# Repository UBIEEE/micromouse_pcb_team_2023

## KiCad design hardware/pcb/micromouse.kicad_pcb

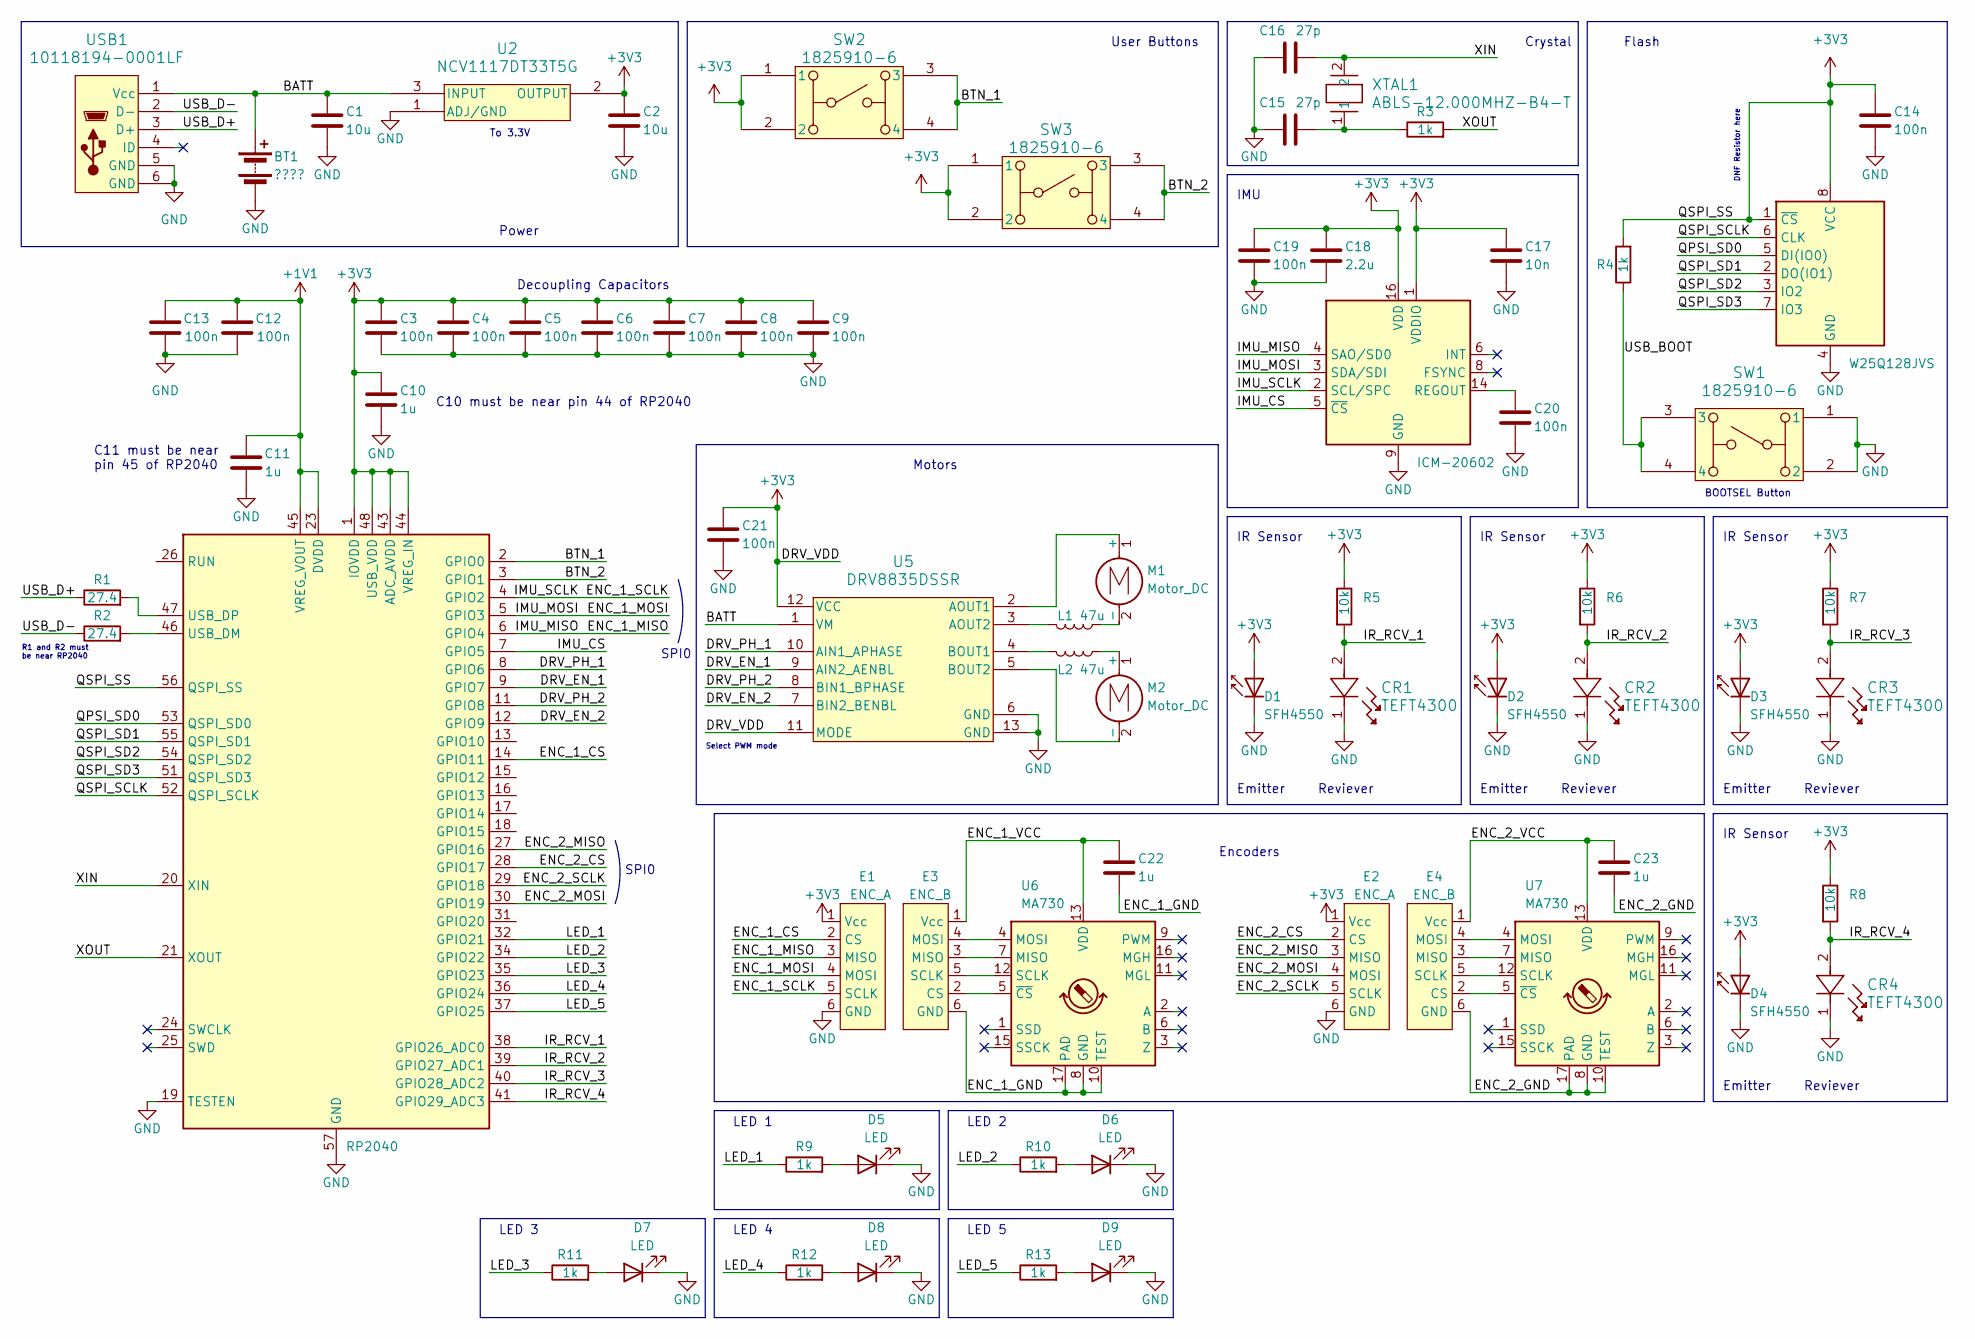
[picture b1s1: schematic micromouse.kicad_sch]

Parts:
BT1: ????; CONN_B2B-ZRLFSN_JST
C1, C2: 10u; CAP_GRM21_MUR
C3, C4, C5, C6, C7, C8, C9, C12, C13, C14, C19, C20, C21: 100n; CAP_GRM155_MUR
C10, C11, C22, C23: 1u; CAP_GRM155_MUR
C15, C16: 27p; CAP_GCM155_MUR
C17: 10n; CAP_GRM1885_1P6XP8_MUR
C18: 2.2u; CAP_GRM155_MUR
CR1, CR2, CR3, CR4: TEFT4300
D1, D2, D3, D4: SFH4550
D5, D6, D7, D8, D9: LED; LED_LTST-C191_LTO
E1: ENC_A; ENC_1_A
E2: ENC_A; ENC_2_A
E3: ENC_B; ENC_1_B
E4: ENC_B; ENC_2_B
L1, L2: 47u; IND_BOURNS_SRR4028
M1, M2: Motor_DC; CONN_B2B-ZRLFSN_JST
R1, R2: 27.4; RES_RC0402_YAG
R3, R4, R9, R10, R11, R12, R13: 1k; RES_RC0402_YAG
R5, R6, R7, R8: 10k; RES_RC0402_YAG
SW1, SW2, SW3: 1825910-6; SW4_1825910-B_TEC
U1: RP2040; QFN-56-1EP_7x7mm_P0.4mm_EP3.2x3.2mm
U2: NCV1117DT33T5G; DPAK-3_ONS
U3: W25Q128JVS; SOIC-8_5.23x5.23mm_P1.27mm
U4: ICM-20602; LGA-16_3x3mm_P0.5mm_LayoutBorder3x5y
U5: DRV8835DSSR; DSS0012A
U6, U7: MA730; QFN-16-1EP_3x3mm_P0.5mm_EP1.75x1.75mm
USB1: 10118194-0001LF; CONN_10118194-0001LF_AMP
XTAL1: ABLS-12.000MHZ-B4-T; XTAL_ABLS_ABR

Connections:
+1V1: C11.2, C12.2, C13.2, U1.23 (DVDD), U1.45 (VREG_VOUT), U1.50 (DVDD)
+3V3: C2.1, C3.1, C4.1, C5.1, C6.1, C7.1, C8.1, C9.1, C10.1, C14.1, C17.1, C18.1, C19.1, C21.1, D1.2 (A), D2.2 (A), D3.2 (A), D4.2 (A), E1.1 (Vcc), E2.1 (Vcc), R4.2, R5.1, R6.1, R7.1, R8.1, SW2.1, SW2.2, SW3.1, SW3.2, U1.1 (IOVDD), U1.10 (IOVDD), U1.22 (IOVDD), U1.33 (IOVDD), U1.42 (IOVDD), U1.43 (ADC_AVDD), U1.44 (VREG_IN), U1.48 (USB_VDD), U1.49 (IOVDD), U1.56 (QSPI_SS), U2.2 (OUTPUT), U3.1 (~CS), U3.8 (VCC), U4.1 (VDDIO), U4.16 (VDD), U5.11 (MODE), U5.12 (VCC)
/BATT: BT1.1 (+), C1.1, U2.3 (INPUT), U5.1 (VM), USB1.1 (Vcc)
/BTN_1: SW2.3, SW2.4, U1.2 (GPIO0)
/BTN_2: SW3.3, SW3.4, U1.3 (GPIO1)
/DRV_EN_1: U1.9 (GPIO7), U5.9 (AIN2_AENBL)
/DRV_EN_2: U1.12 (GPIO9), U5.7 (BIN2_BENBL)
/DRV_PH_1: U1.8 (GPIO6), U5.10 (AIN1_APHASE)
/DRV_PH_2: U1.11 (GPIO8), U5.8 (BIN1_BPHASE)
/ENC_1_CS: E1.2 (CS), U1.14 (GPIO11)
/ENC_1_GND: C22.2, E3.6 (GND), U6.8 (GND), U6.10 (TEST), U6.17 (PAD)
/ENC_1_MISO: E1.3 (MISO), U1.6 (GPIO4), U4.4 (SAO/SD0)
/ENC_1_MOSI: E1.4 (MOSI), U1.5 (GPIO3), U4.3 (SDA/SDI)
/ENC_1_SCLK: E1.5 (SCLK), U1.4 (GPIO2), U4.2 (SCL/SPC)
/ENC_1_VCC: C22.1, E3.1 (Vcc), U6.13 (VDD)
/ENC_2_CS: E2.2 (CS), U1.28 (GPIO17)
/ENC_2_GND: C23.2, E4.6 (GND), U7.8 (GND), U7.10 (TEST), U7.17 (PAD)
/ENC_2_MISO: E2.3 (MISO), U1.27 (GPIO16)
/ENC_2_MOSI: E2.4 (MOSI), U1.30 (GPIO19)
/ENC_2_SCLK: E2.5 (SCLK), U1.29 (GPIO18)
/ENC_2_VCC: C23.1, E4.1 (Vcc), U7.13 (VDD)
/IMU_CS: U1.7 (GPIO5), U4.5 (~CS)
/IR_RCV_1: CR1.2, R5.2, U1.38 (GPIO26_ADC0)
/IR_RCV_2: CR2.2, R6.2, U1.39 (GPIO27_ADC1)
/IR_RCV_3: CR3.2, R7.2, U1.40 (GPIO28_ADC2)
/IR_RCV_4: CR4.2, R8.2, U1.41 (GPIO29_ADC3)
/LED_1: R9.1, U1.32 (GPIO21)
/LED_2: R10.1, U1.34 (GPIO22)
/LED_3: R11.1, U1.35 (GPIO23)
/LED_4: R12.1, U1.36 (GPIO24)
/LED_5: R13.1, U1.37 (GPIO25)
/QPSI_SD0: U1.53 (QSPI_SD0), U3.5 (DI(IO0))
/QSPI_SCLK: U1.52 (QSPI_SCLK), U3.6 (CLK)
/QSPI_SD1: U1.55 (QSPI_SD1), U3.2 (DO(IO1))
/QSPI_SD2: U1.54 (QSPI_SD2), U3.3 (IO2)
/QSPI_SD3: U1.51 (QSPI_SD3), U3.7 (IO3)
/USB_BOOT: R4.1, SW1.3, SW1.4
/USB_D+: R1.1, USB1.3 (D+)
/USB_D-: R2.1, USB1.2 (D-)
/XIN: C16.2, U1.20 (XIN), XTAL1.2
/XOUT: R3.2, U1.21 (XOUT)
GND: BT1.2 (-), C1.2, C2.2, C3.2, C4.2, C5.2, C6.2, C7.2, C8.2, C9.2, C10.2, C11.1, C12.1, C13.1, C14.2, C15.1, C16.1, C17.2, C18.2, C19.2, C20.2, C21.2, CR1.1, CR2.1, CR3.1, CR4.1, D1.1 (K), D2.1 (K), D3.1 (K), D4.1 (K), D5.1 (K), D6.1 (K), D7.1 (K), D8.1 (K), D9.1 (K), E1.6 (GND), E2.6 (GND), SW1.1, SW1.2, U1.19 (TESTEN), U1.57 (GND), U2.1 (ADJ/GND), U3.4 (GND), U4.9 (GND), U4.10 (GND), U4.11 (GND), U4.12 (GND), U4.13 (GND), U4.15 (GND), U5.6 (GND), U5.13 (GND), USB1.5 (GND), USB1.6 (GND)
unnamed: C15.2, R3.1, XTAL1.1
unnamed: D5.2 (A), R9.2
unnamed: D6.2 (A), R10.2
unnamed: D7.2 (A), R11.2
unnamed: D8.2 (A), R12.2
unnamed: D9.2 (A), R13.2
unnamed: E3.2 (CS), U6.5 (~CS)
unnamed: E3.3 (MISO), U6.7 (MISO)
unnamed: E3.4 (MOSI), U6.4 (MOSI)
unnamed: E3.5 (SCLK), U6.12 (SCLK)
unnamed: E4.2 (CS), U7.5 (~CS)
unnamed: E4.3 (MISO), U7.7 (MISO)
unnamed: E4.4 (MOSI), U7.4 (MOSI)
unnamed: E4.5 (SCLK), U7.12 (SCLK)
unnamed: M1.1 (+), U5.2 (AOUT1)
unnamed: L1.1, M1.2 (-)
unnamed: L2.1, M2.1 (+)
unnamed: M2.2 (-), U5.5 (BOUT2)
unnamed: R2.2, U1.46 (USB_DM)
unnamed: R1.2, U1.47 (USB_DP)
unnamed: C20.1, U4.14 (REGOUT)
unnamed: L1.2, U5.3 (AOUT2)
unnamed: L2.2, U5.4 (BOUT1)

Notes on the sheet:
Decoupling Capacitors
User Buttons
Emitter
Reviever
LED 4
LED 3
Flash
Crystal
DNF Resistor here
Select PWM mode
Power
SPI0
R1 and R2 must be near RP2040
IR Sensor
BOOTSEL Button
Encoders
C11 must be near pin 45 of RP2040
To 3.3V
LED 5
LED 1
C10 must be near pin 44 of RP2040
LED 2
IMU
Motors

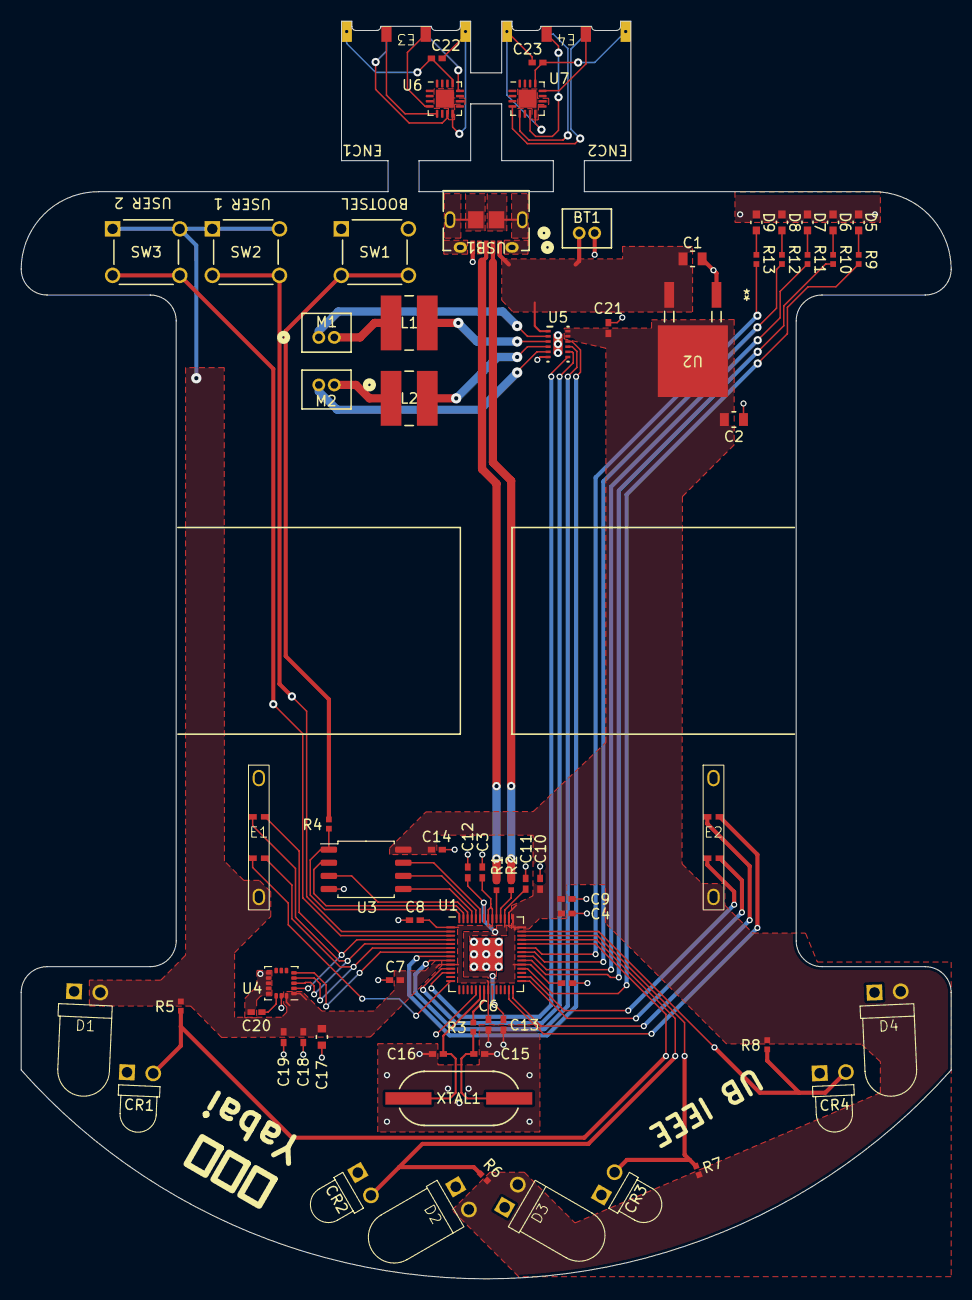
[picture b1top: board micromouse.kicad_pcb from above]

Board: 2 copper layers, 90.0 x 121.7 mm, 70 parts (0 on the bottom side), 65 nets.

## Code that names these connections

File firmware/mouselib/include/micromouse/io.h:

#ifndef __MICROMOUSE_IO_H__
#define __MICROMOUSE_IO_H__

#define PIN_BTN_1 0
#define PIN_BTN_2 1

// SPI 0
#define PIN_IMU_R_ENC_SCLK 2
#define PIN_IMU_R_ENC_MOSI 3
#define PIN_IMU_R_ENC_MISO 4
#define PIN_IMU_CS         5

#define PIN_L_MOT_PH 6
#define PIN_L_MOT_EN 7

#define PIN_R_MOT_PH 8
#define PIN_R_MOT_EN 9

// 10 - Unused

#define PIN_R_ENC_CS 11

// 12 - Unused
// 13 - Unused
// 14 - Unused
// 15 - Unused

// SPI 0
#define PIN_L_ENC_SCLK 18
#define PIN_L_ENC_MOSI 19
#define PIN_L_ENC_MISO 16
#define PIN_L_ENC_CS   17

// 20 - Unused

#define PIN_LED_1 21
#define PIN_LED_2 22
#define PIN_LED_3 23
#define PIN_LED_4 24
#define PIN_LED_5 25

#define PIN_ADC_0 26
#define PIN_ADC_1 27
#define PIN_ADC_2 28
#define PIN_ADC_3 29

#endif // __MICROMOUSE_IO_H__

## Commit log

2023-10-21 Added gitignore
2023-10-21 Initial work on PCB schematic
2023-10-22 Created initial CMake project
2023-10-25 Started work on PCB, still got a lot of work to do
2023-10-27 Lots of PCB work
2023-11-07 PCB updates
2023-11-08 Removed extra silkscreen drawings and stuff on the side
2023-11-26 Initial code for drivetrain and MA730 encoders
2023-11-26 Fixed some DRC errors, worked on encoder placement
2023-11-30 Updated hardware IO, worked on ICM20602 and MA730 hardware drivers, drivetrain, etc.
2023-12-01 Created PWM hardware driver for DRV8835 motor driver, cleanup, etc.
2023-12-01 Created test programs for imu and encoders
2024-01-07 Final PCB updates??
2024-01-17 Some small firmware updates
2024-01-28 Code is organized better now
2024-01-28 Created mutex to protect state
2024-01-30 Moved to C++
2024-02-08 Created logic library and ability for desktop testing
2024-02-08 Updated gitignore
2024-02-18 Added GoogleTest
2024-02-18 Upgraded to C++ 20
2024-02-20 Simple cell and maze classes, wrote tests
2024-03-10 Cleaned up stuff
2024-03-11 Added Illumination subsystem
